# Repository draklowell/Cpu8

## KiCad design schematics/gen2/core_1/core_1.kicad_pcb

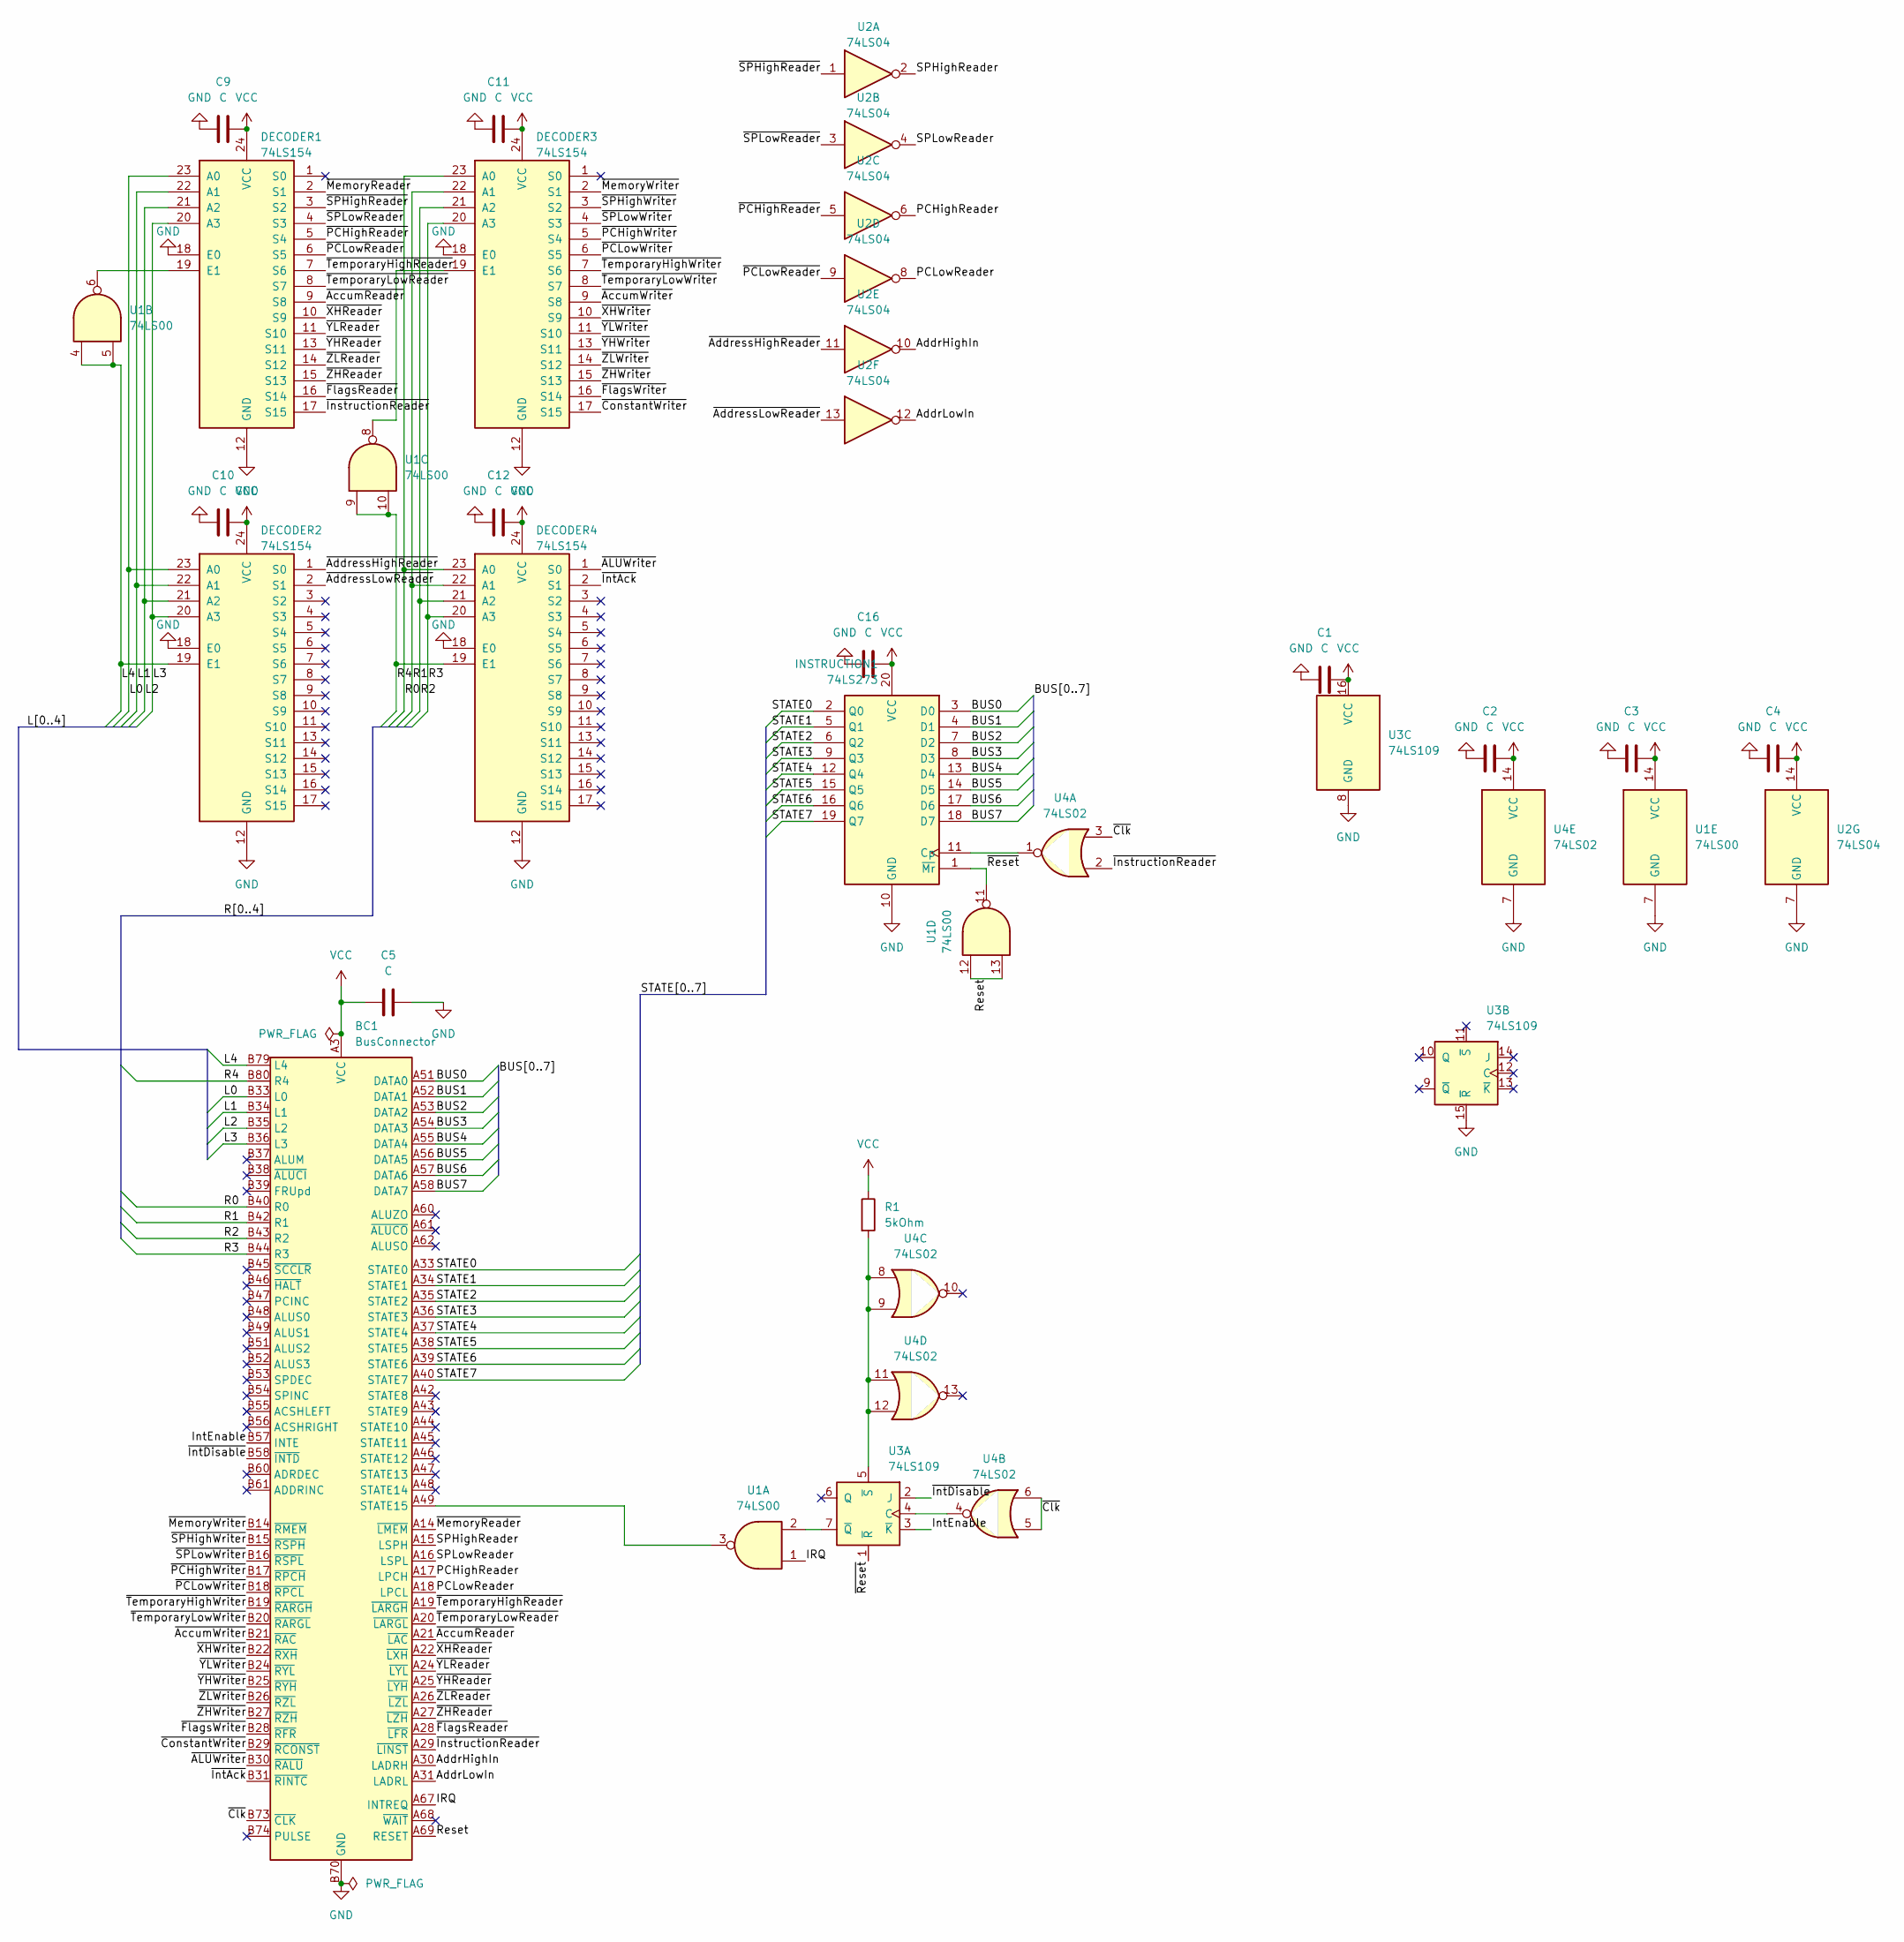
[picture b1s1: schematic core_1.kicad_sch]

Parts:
BC1: BusConnector; BUS_PCIexpress_x16
C1, C2, C3, C4, C9, C10, C11, C12, C16: C; C_Disc_D5.0mm_W2.5mm_P2.50mm
C5: C; C_Radial_D6.3mm_H5.0mm_P2.50mm
DECODER1, DECODER2, DECODER3, DECODER4: 74LS154; DIP-24_W7.62mm_Socket_LongPads
INSTRUCTION1: 74LS273; DIP-20_W7.62mm_Socket_LongPads
R1: 5kOhm; R_Axial_DIN0207_L6.3mm_D2.5mm_P7.62mm_Horizontal
U1: 74LS00; DIP-14_W7.62mm_Socket_LongPads
U2: 74LS04; DIP-14_W7.62mm_Socket_LongPads
U3: 74LS109; DIP-16_W7.62mm_Socket_LongPads
U4: 74LS02; DIP-14_W7.62mm_Socket_LongPads

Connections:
/AddrHighIn: BC1.A30 (LADRH), U2.10
/AddrLowIn: BC1.A31 (LADRL), U2.12
/BUS0: BC1.A51 (DATA0), INSTRUCTION1.3 (D0)
/BUS1: BC1.A52 (DATA1), INSTRUCTION1.4 (D1)
/BUS2: BC1.A53 (DATA2), INSTRUCTION1.7 (D2)
/BUS3: BC1.A54 (DATA3), INSTRUCTION1.8 (D3)
/BUS4: BC1.A55 (DATA4), INSTRUCTION1.13 (D4)
/BUS5: BC1.A56 (DATA5), INSTRUCTION1.14 (D5)
/BUS6: BC1.A57 (DATA6), INSTRUCTION1.17 (D6)
/BUS7: BC1.A58 (DATA7), INSTRUCTION1.18 (D7)
/IRQ: BC1.A67 (INTREQ), U1.1
/IntEnable: BC1.B57 (INTE), U3.3 (~K)
/L0: BC1.B33 (L0), DECODER1.23 (A0), DECODER2.23 (A0)
/L1: BC1.B34 (L1), DECODER1.22 (A1), DECODER2.22 (A1)
/L2: BC1.B35 (L2), DECODER1.21 (A2), DECODER2.21 (A2)
/L3: BC1.B36 (L3), DECODER1.20 (A3), DECODER2.20 (A3)
/L4: BC1.B79 (L4), DECODER2.19 (E1), U1.4, U1.5
/PCHighReader: BC1.A17 (LPCH), U2.6
/PCLowReader: BC1.A18 (LPCL), U2.8
/R0: BC1.B40 (R0), DECODER3.23 (A0), DECODER4.23 (A0)
/R1: BC1.B42 (R1), DECODER3.22 (A1), DECODER4.22 (A1)
/R2: BC1.B43 (R2), DECODER3.21 (A2), DECODER4.21 (A2)
/R3: BC1.B44 (R3), DECODER3.20 (A3), DECODER4.20 (A3)
/R4: BC1.B80 (R4), DECODER4.19 (E1), U1.9, U1.10
/Reset: BC1.A69 (RESET), U1.12, U1.13
/SPHighReader: BC1.A15 (LSPH), U2.2
/SPLowReader: BC1.A16 (LSPL), U2.4
/STATE0: BC1.A33 (STATE0), INSTRUCTION1.2 (Q0)
/STATE1: BC1.A34 (STATE1), INSTRUCTION1.5 (Q1)
/STATE2: BC1.A35 (STATE2), INSTRUCTION1.6 (Q2)
/STATE3: BC1.A36 (STATE3), INSTRUCTION1.9 (Q3)
/STATE4: BC1.A37 (STATE4), INSTRUCTION1.12 (Q4)
/STATE5: BC1.A38 (STATE5), INSTRUCTION1.15 (Q5)
/STATE6: BC1.A39 (STATE6), INSTRUCTION1.16 (Q6)
/STATE7: BC1.A40 (STATE7), INSTRUCTION1.19 (Q7)
/~ALUWriter: BC1.B30 (~RALU), DECODER4.1 (S0)
/~AccumReader: BC1.A21 (~LAC), DECODER1.9 (S8)
/~AccumWriter: BC1.B21 (~RAC), DECODER3.9 (S8)
/~AddressHighReader: DECODER2.1 (S0), U2.11
/~AddressLowReader: DECODER2.2 (S1), U2.13
/~Clk: BC1.B73 (~CLK), U4.3, U4.5, U4.6
/~ConstantWriter: BC1.B29 (~RCONST), DECODER3.17 (S15)
/~FlagsReader: BC1.A28 (~LFR), DECODER1.16 (S14)
/~FlagsWriter: BC1.B28 (~RFR), DECODER3.16 (S14)
/~InstructionReader: BC1.A29 (~LINST), DECODER1.17 (S15), U4.2
/~IntAck: BC1.B31 (~RINTC), DECODER4.2 (S1)
/~IntDisable: BC1.B58 (~INTD), U3.2 (J)
/~MemoryReader: BC1.A14 (~LMEM), DECODER1.2 (S1)
/~MemoryWriter: BC1.B14 (~RMEM), DECODER3.2 (S1)
/~PCHighReader: DECODER1.5 (S4), U2.5
/~PCHighWriter: BC1.B17 (~RPCH), DECODER3.5 (S4)
/~PCLowReader: DECODER1.6 (S5), U2.9
/~PCLowWriter: BC1.B18 (~RPCL), DECODER3.6 (S5)
/~Reset: INSTRUCTION1.1 (~Mr), U1.11, U3.1 (~R)
/~SPHighReader: DECODER1.3 (S2), U2.1
/~SPHighWriter: BC1.B15 (~RSPH), DECODER3.3 (S2)
/~SPLowReader: DECODER1.4 (S3), U2.3
/~SPLowWriter: BC1.B16 (~RSPL), DECODER3.4 (S3)
/~TemporaryHighReader: BC1.A19 (~LARGH), DECODER1.7 (S6)
/~TemporaryHighWriter: BC1.B19 (~RARGH), DECODER3.7 (S6)
/~TemporaryLowReader: BC1.A20 (~LARGL), DECODER1.8 (S7)
/~TemporaryLowWriter: BC1.B20 (~RARGL), DECODER3.8 (S7)
/~XHReader: BC1.A22 (~LXH), DECODER1.10 (S9)
/~XHWriter: BC1.B22 (~RXH), DECODER3.10 (S9)
/~YHReader: BC1.A25 (~LYH), DECODER1.13 (S11)
/~YHWriter: BC1.B25 (~RYH), DECODER3.13 (S11)
/~YLReader: BC1.A24 (~LYL), DECODER1.11 (S10)
/~YLWriter: BC1.B24 (~RYL), DECODER3.11 (S10)
/~ZHReader: BC1.A27 (~LZH), DECODER1.15 (S13)
/~ZHWriter: BC1.B27 (~RZH), DECODER3.15 (S13)
/~ZLReader: BC1.A26 (~LZL), DECODER1.14 (S12)
/~ZLWriter: BC1.B26 (~RZL), DECODER3.14 (S12)
GND: BC1.A12 (GND), BC1.A13 (GND), BC1.A23 (GND), BC1.A32 (GND), BC1.A41 (GND), BC1.A50 (GND), BC1.A59 (GND), BC1.A63 (GND), BC1.A64 (GND), BC1.A65 (GND), BC1.A66 (GND), BC1.A70 (GND), BC1.A71 (GND), BC1.A72 (GND), BC1.A73 (GND), BC1.A74 (GND), BC1.A75 (GND), BC1.A76 (GND), BC1.B12 (GND), BC1.B13 (GND), BC1.B23 (GND), BC1.B32 (GND), BC1.B41 (GND), BC1.B50 (GND), BC1.B59 (GND), BC1.B62 (GND), BC1.B63 (GND), BC1.B64 (GND), BC1.B65 (GND), BC1.B66 (GND), BC1.B67 (GND), BC1.B68 (GND), BC1.B69 (GND), BC1.B70 (GND), BC1.B71 (GND), BC1.B72 (GND), BC1.B75 (GND), BC1.B76 (GND), C1.2, C2.2, C3.2, C4.2, C5.2, C9.2, C10.2, C11.2, C12.2, C16.2, DECODER1.12 (GND), DECODER1.18 (E0), DECODER2.12 (GND), DECODER2.18 (E0), DECODER3.12 (GND), DECODER3.18 (E0), DECODER4.12 (GND), DECODER4.18 (E0), INSTRUCTION1.10 (GND), U1.7 (GND), U2.7 (GND), U3.8 (GND), U3.15 (~R), U4.7 (GND)
unnamed: BC1.A49 (STATE15), U1.3
unnamed: DECODER1.19 (E1), U1.6
unnamed: DECODER3.19 (E1), U1.8
unnamed: INSTRUCTION1.11 (Cp), U4.1
unnamed: U3.4 (C), U4.4
unnamed: U1.2, U3.7 (~Q)
unnamed: R1.2, U3.5 (~S), U4.8, U4.9, U4.11, U4.12
VCC: BC1.A1 (VCC), BC1.A2 (VCC), BC1.A3 (VCC), BC1.A4 (VCC), BC1.A5 (VCC), BC1.B1 (VCC), BC1.B2 (VCC), BC1.B3 (VCC), BC1.B4 (VCC), BC1.B5 (VCC), C1.1, C2.1, C3.1, C4.1, C5.1, C9.1, C10.1, C11.1, C12.1, C16.1, DECODER1.24 (VCC), DECODER2.24 (VCC), DECODER3.24 (VCC), DECODER4.24 (VCC), INSTRUCTION1.20 (VCC), R1.1, U1.14 (VCC), U2.14 (VCC), U3.16 (VCC), U4.14 (VCC)

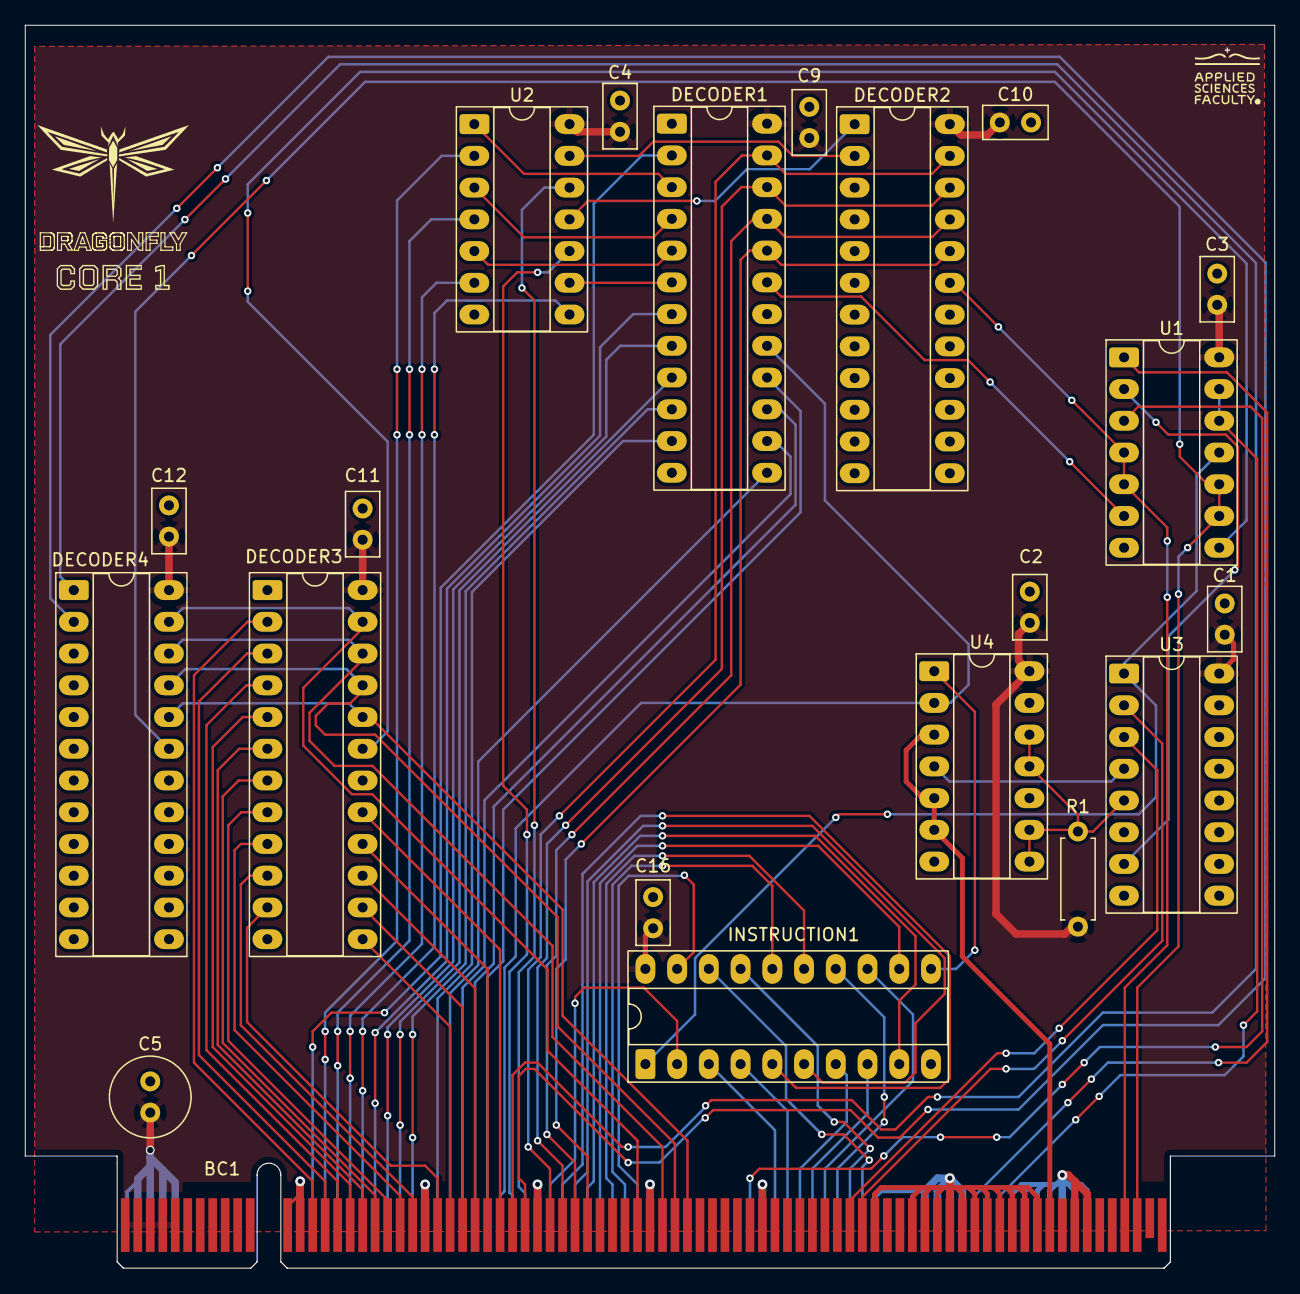
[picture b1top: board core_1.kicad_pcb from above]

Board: 2 copper layers, 100.0 x 99.5 mm, 22 parts (0 on the bottom side), 81 nets.

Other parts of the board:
kibuzzard-6911CC41: G***; kibuzzard-6911CC41

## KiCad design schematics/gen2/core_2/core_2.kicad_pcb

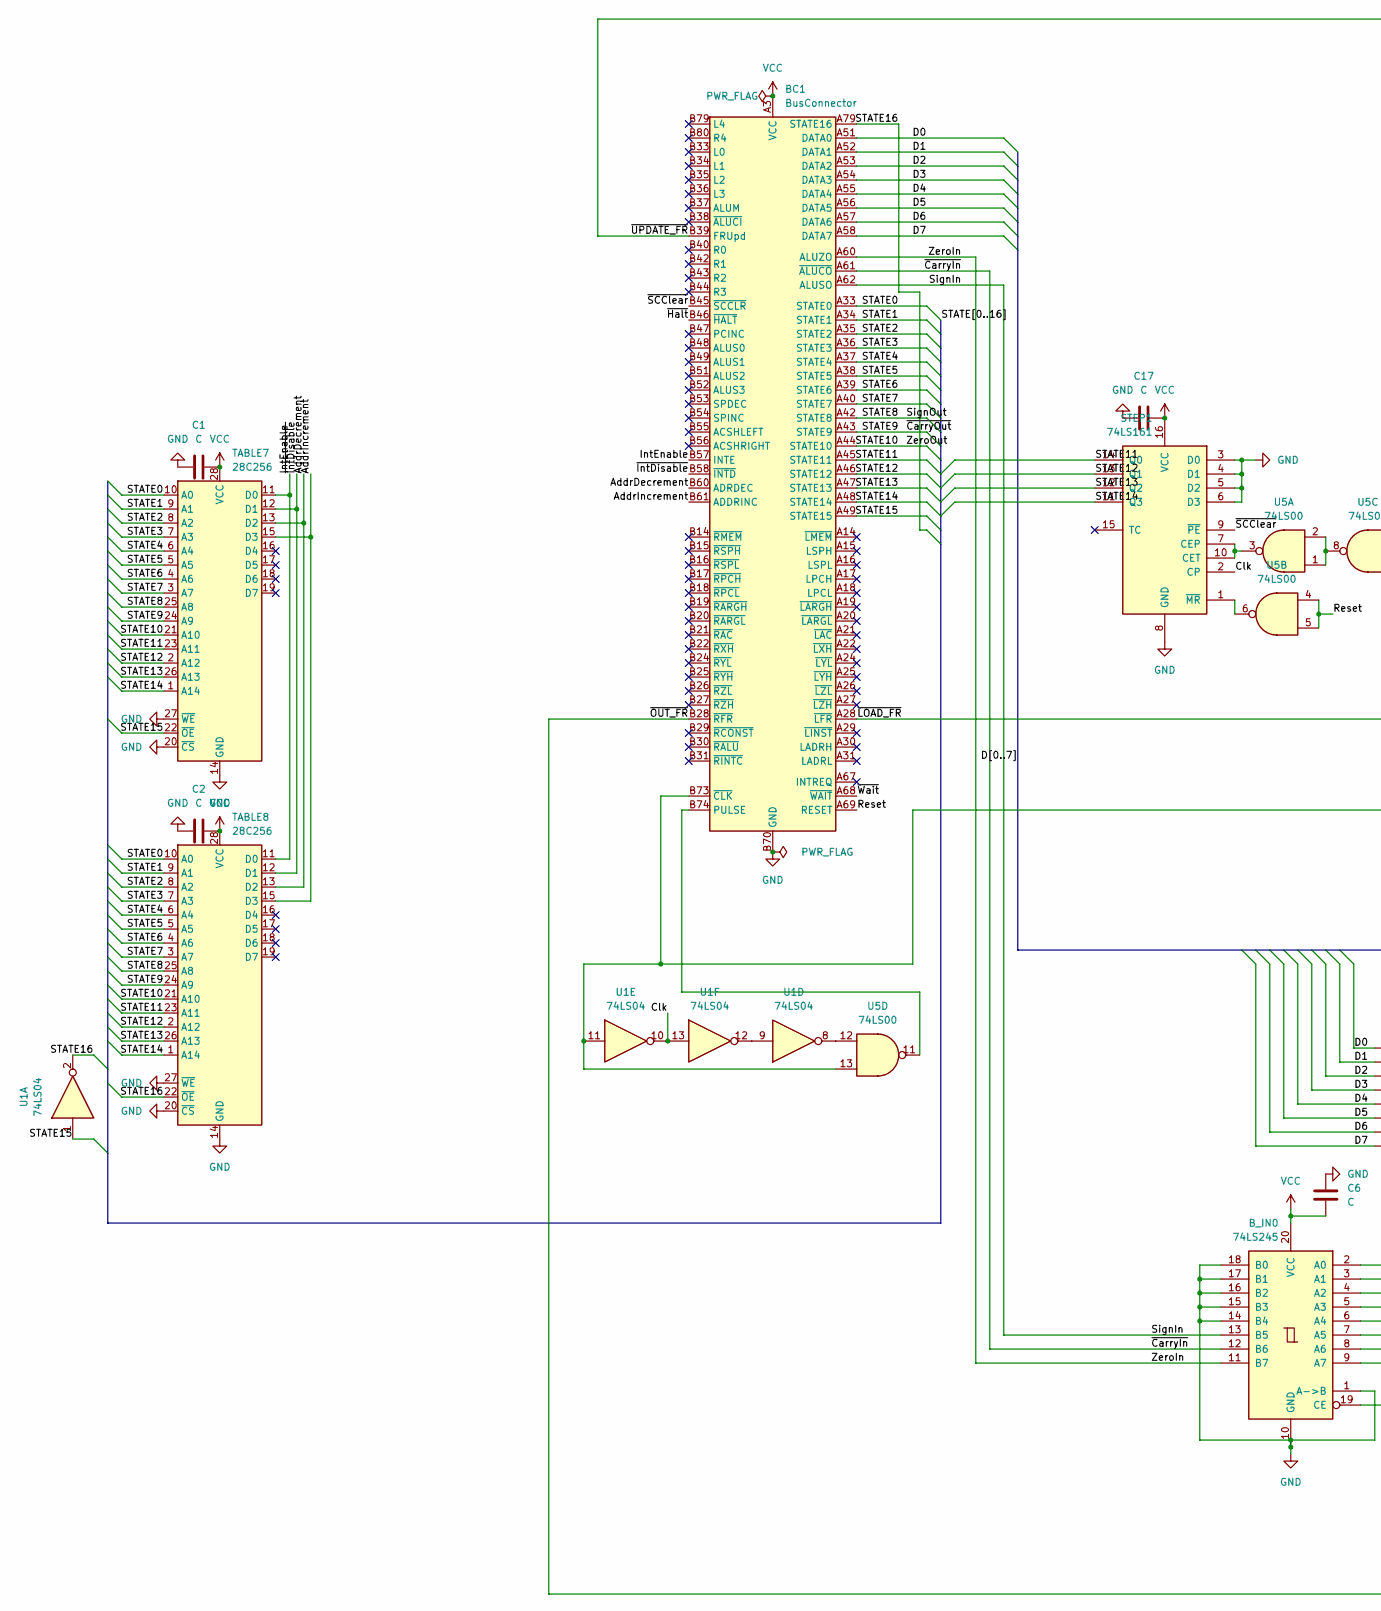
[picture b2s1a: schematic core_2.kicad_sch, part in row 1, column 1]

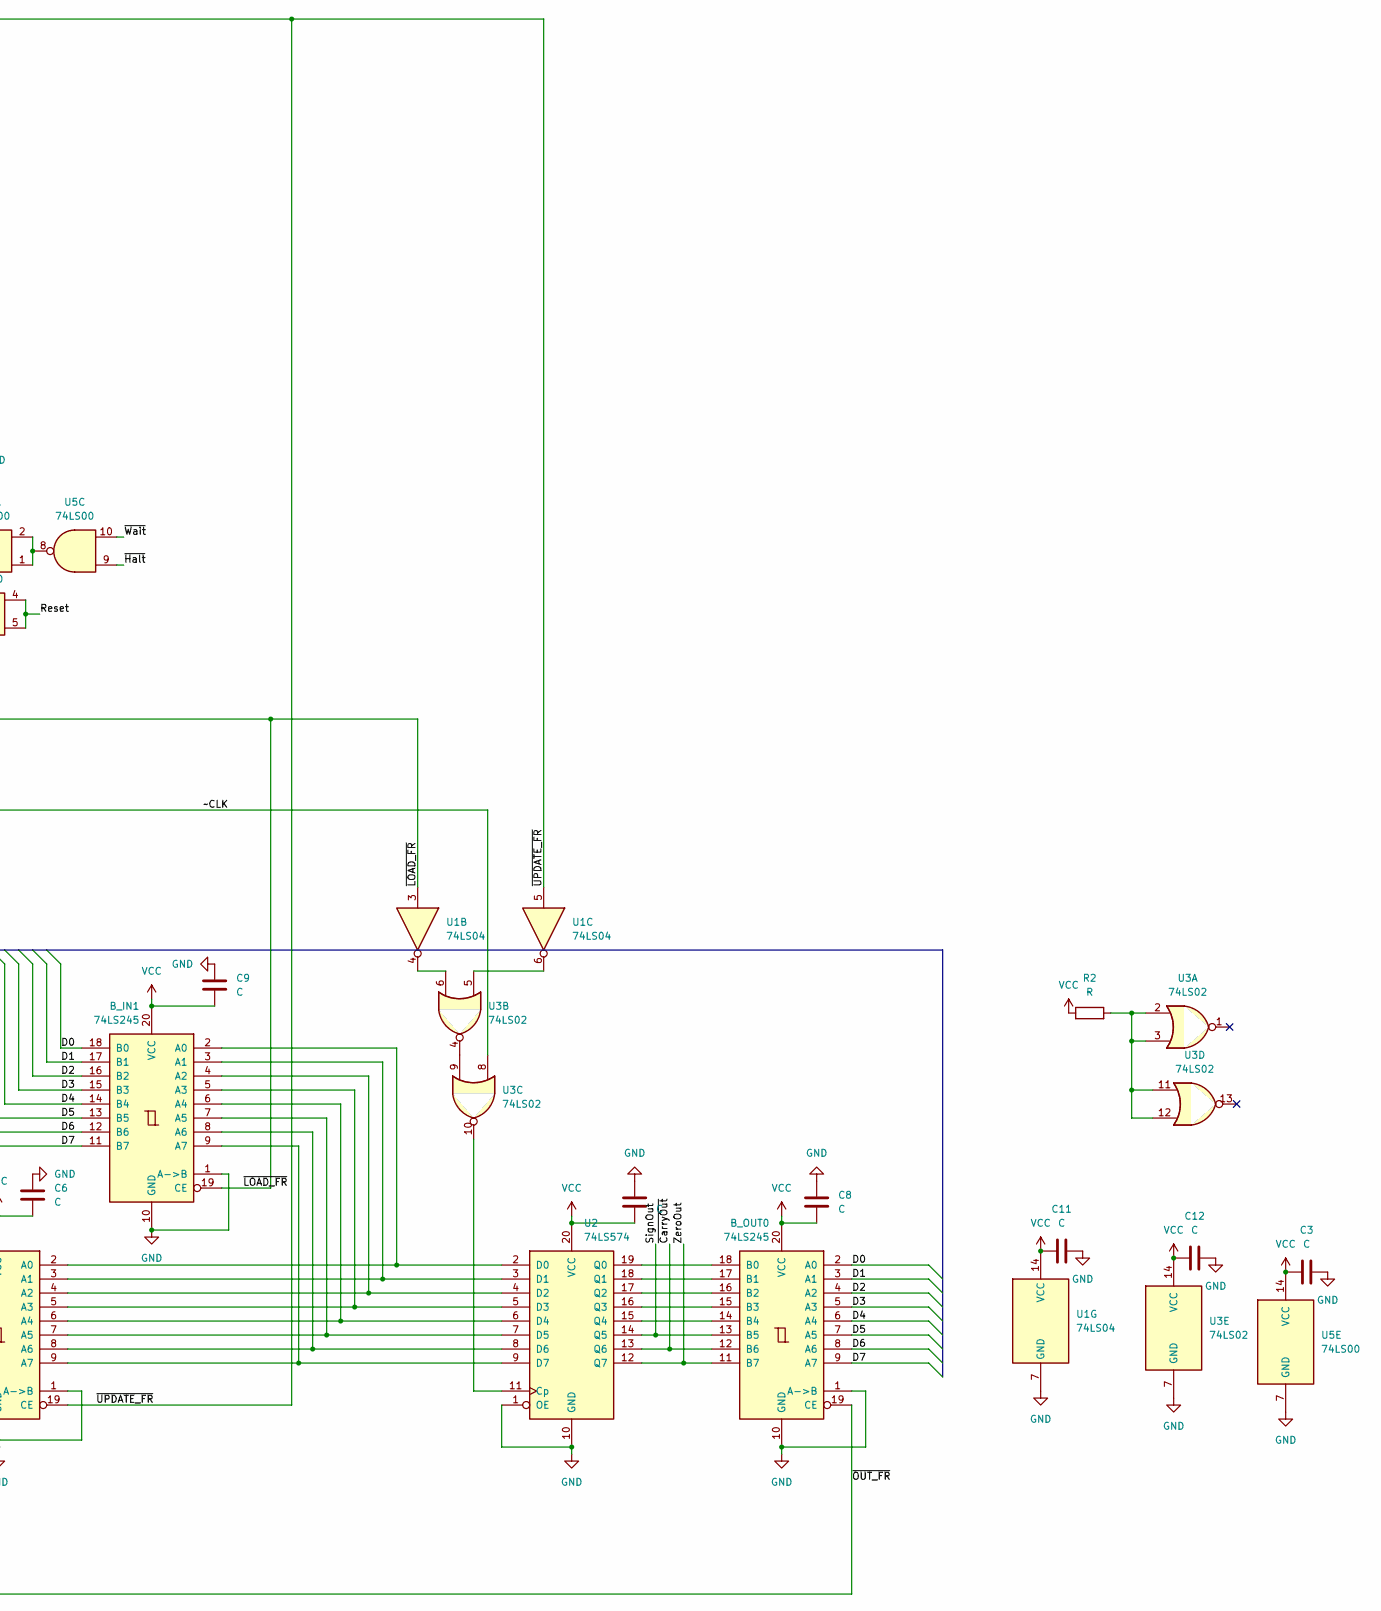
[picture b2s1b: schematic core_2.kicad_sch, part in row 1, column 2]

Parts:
BC1: BusConnector; BUS_PCIexpress_x16
B_IN0, B_IN1: 74LS245; DIP-20_W7.62mm_Socket_LongPads
B_OUT0: 74LS245; DIP-20_W7.62mm_Socket_LongPads
C1, C2, C3, C6, C7, C8, C9, C11, C12, C17: C; C_Disc_D5.0mm_W2.5mm_P5.00mm
R2: R; R_Axial_DIN0207_L6.3mm_D2.5mm_P7.62mm_Horizontal
STEP1: 74LS161; DIP-16_W7.62mm_Socket_LongPads
TABLE7, TABLE8: 28C256; DIP-28_W15.24mm_Socket_LongPads
U1: 74LS04; DIP-14_W7.62mm_Socket_LongPads
U2: 74LS574; DIP-20_W7.62mm_Socket_LongPads
U3: 74LS02; DIP-14_W7.62mm_Socket_LongPads
U5: 74LS00; DIP-14_W7.62mm_Socket_LongPads

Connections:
/AddrDecrement: BC1.B60 (ADRDEC), TABLE7.13 (D2), TABLE8.13 (D2)
/AddrIncrement: BC1.B61 (ADDRINC), TABLE7.15 (D3), TABLE8.15 (D3)
/Clk: STEP1.2 (CP), U1.10, U1.13
/D0: BC1.A51 (DATA0), B_IN1.18 (B0), B_OUT0.2 (A0)
/D1: BC1.A52 (DATA1), B_IN1.17 (B1), B_OUT0.3 (A1)
/D2: BC1.A53 (DATA2), B_IN1.16 (B2), B_OUT0.4 (A2)
/D3: BC1.A54 (DATA3), B_IN1.15 (B3), B_OUT0.5 (A3)
/D4: BC1.A55 (DATA4), B_IN1.14 (B4), B_OUT0.6 (A4)
/D5: BC1.A56 (DATA5), B_IN1.13 (B5), B_OUT0.7 (A5)
/D6: BC1.A57 (DATA6), B_IN1.12 (B6), B_OUT0.8 (A6)
/D7: BC1.A58 (DATA7), B_IN1.11 (B7), B_OUT0.9 (A7)
/IntEnable: BC1.B57 (INTE), TABLE7.11 (D0), TABLE8.11 (D0)
/Reset: BC1.A69 (RESET), U5.4, U5.5
/STATE0: BC1.A33 (STATE0), TABLE7.10 (A0), TABLE8.10 (A0)
/STATE1: BC1.A34 (STATE1), TABLE7.9 (A1), TABLE8.9 (A1)
/STATE2: BC1.A35 (STATE2), TABLE7.8 (A2), TABLE8.8 (A2)
/STATE3: BC1.A36 (STATE3), TABLE7.7 (A3), TABLE8.7 (A3)
/STATE4: BC1.A37 (STATE4), TABLE7.6 (A4), TABLE8.6 (A4)
/STATE5: BC1.A38 (STATE5), TABLE7.5 (A5), TABLE8.5 (A5)
/STATE6: BC1.A39 (STATE6), TABLE7.4 (A6), TABLE8.4 (A6)
/STATE7: BC1.A40 (STATE7), TABLE7.3 (A7), TABLE8.3 (A7)
/STATE8: BC1.A42 (STATE8), B_OUT0.13 (B5), TABLE7.25 (A8), TABLE8.25 (A8), U2.14 (Q5)
/STATE9: BC1.A43 (STATE9), B_OUT0.12 (B6), TABLE7.24 (A9), TABLE8.24 (A9), U2.13 (Q6)
/STATE10: BC1.A44 (STATE10), B_OUT0.11 (B7), TABLE7.21 (A10), TABLE8.21 (A10), U2.12 (Q7)
/STATE11: BC1.A45 (STATE11), STEP1.14 (Q0), TABLE7.23 (A11), TABLE8.23 (A11)
/STATE12: BC1.A46 (STATE12), STEP1.13 (Q1), TABLE7.2 (A12), TABLE8.2 (A12)
/STATE13: BC1.A47 (STATE13), STEP1.12 (Q2), TABLE7.26 (A13), TABLE8.26 (A13)
/STATE14: BC1.A48 (STATE14), STEP1.11 (Q3), TABLE7.1 (A14), TABLE8.1 (A14)
/STATE15: BC1.A49 (STATE15), TABLE7.22 (~OE), U1.1
/STATE16: BC1.A79 (STATE16), TABLE8.22 (~OE), U1.2
/SignIn: BC1.A62 (ALUSO), B_IN0.13 (B5)
/ZeroIn: BC1.A60 (ALUZO), B_IN0.11 (B7)
/~CLK: BC1.B73 (~CLK), U1.11, U3.8, U5.13
/~CarryIn: BC1.A61 (~ALUCO), B_IN0.12 (B6)
/~Halt: BC1.B46 (~HALT), U5.9
/~IntDisable: BC1.B58 (~INTD), TABLE7.12 (D1), TABLE8.12 (D1)
/~LOAD_FR: BC1.A28 (~LFR), B_IN1.19 (CE), U1.3
/~OUT_FR: BC1.B28 (~RFR), B_OUT0.19 (CE)
/~SCClear: BC1.B45 (~SCCLR), STEP1.9 (~PE)
/~UPDATE_FR: BC1.B39 (FRUpd), B_IN0.19 (CE), U1.5
/~Wait: BC1.A68 (~WAIT), U5.10
GND: BC1.A12 (GND), BC1.A13 (GND), BC1.A23 (GND), BC1.A32 (GND), BC1.A41 (GND), BC1.A50 (GND), BC1.A59 (GND), BC1.A63 (GND), BC1.A64 (GND), BC1.A65 (GND), BC1.A66 (GND), BC1.A70 (GND), BC1.A71 (GND), BC1.A72 (GND), BC1.A73 (GND), BC1.A74 (GND), BC1.A75 (GND), BC1.A76 (GND), BC1.B12 (GND), BC1.B13 (GND), BC1.B23 (GND), BC1.B32 (GND), BC1.B41 (GND), BC1.B50 (GND), BC1.B59 (GND), BC1.B62 (GND), BC1.B63 (GND), BC1.B64 (GND), BC1.B65 (GND), BC1.B66 (GND), BC1.B67 (GND), BC1.B68 (GND), BC1.B69 (GND), BC1.B70 (GND), BC1.B71 (GND), BC1.B72 (GND), BC1.B75 (GND), BC1.B76 (GND), B_IN0.1 (A->B), B_IN0.10 (GND), B_IN0.14 (B4), B_IN0.15 (B3), B_IN0.16 (B2), B_IN0.17 (B1), B_IN0.18 (B0), B_IN1.1 (A->B), B_IN1.10 (GND), B_OUT0.1 (A->B), B_OUT0.10 (GND), C1.2, C2.2, C3.2, C6.1, C7.1, C8.1, C9.1, C11.2, C12.2, C17.2, STEP1.3 (D0), STEP1.4 (D1), STEP1.5 (D2), STEP1.6 (D3), STEP1.8 (GND), TABLE7.14 (GND), TABLE7.20 (~CS), TABLE7.27 (~WE), TABLE8.14 (GND), TABLE8.20 (~CS), TABLE8.27 (~WE), U1.7 (GND), U2.1 (OE), U2.10 (GND), U3.7 (GND), U5.7 (GND); also elsewhere on the board
unnamed: BC1.B74 (PULSE), U5.11
unnamed: B_IN0.2 (A0), B_IN1.2 (A0), U2.2 (D0)
unnamed: B_IN0.3 (A1), B_IN1.3 (A1), U2.3 (D1)
unnamed: B_IN0.4 (A2), B_IN1.4 (A2), U2.4 (D2)
unnamed: B_IN0.5 (A3), B_IN1.5 (A3), U2.5 (D3)
unnamed: B_IN0.6 (A4), B_IN1.6 (A4), U2.6 (D4)
unnamed: B_IN0.7 (A5), B_IN1.7 (A5), U2.7 (D5)
unnamed: B_IN0.8 (A6), B_IN1.8 (A6), U2.8 (D6)
unnamed: B_IN0.9 (A7), B_IN1.9 (A7), U2.9 (D7)
unnamed: B_OUT0.18 (B0), U2.19 (Q0)
unnamed: B_OUT0.17 (B1), U2.18 (Q1)
unnamed: B_OUT0.16 (B2), U2.17 (Q2)
unnamed: B_OUT0.15 (B3), U2.16 (Q3)
unnamed: B_OUT0.14 (B4), U2.15 (Q4)
unnamed: R2.2, U3.2, U3.3, U3.11, U3.12
unnamed: STEP1.7 (CEP), STEP1.10 (CET), U5.3
unnamed: STEP1.1 (~MR), U5.6
unnamed: U1.4, U3.6
unnamed: U1.6, U3.5
unnamed: U1.8, U5.12
unnamed: U1.9, U1.12
unnamed: U2.11 (Cp), U3.10
unnamed: U3.4, U3.9
unnamed: U5.1, U5.2, U5.8
VCC: BC1.A1 (VCC), BC1.A2 (VCC), BC1.A3 (VCC), BC1.A4 (VCC), BC1.A5 (VCC), BC1.B1 (VCC), BC1.B2 (VCC), BC1.B3 (VCC), BC1.B4 (VCC), BC1.B5 (VCC), B_IN0.20 (VCC), B_IN1.20 (VCC), B_OUT0.20 (VCC), C1.1, C2.1, C3.1, C6.2, C7.2, C8.2, C9.2, C11.1, C12.1, C17.1, R2.1, STEP1.16 (VCC), TABLE7.28 (VCC), TABLE8.28 (VCC), U1.14 (VCC), U2.20 (VCC), U3.14 (VCC), U5.14 (VCC); also elsewhere on the board

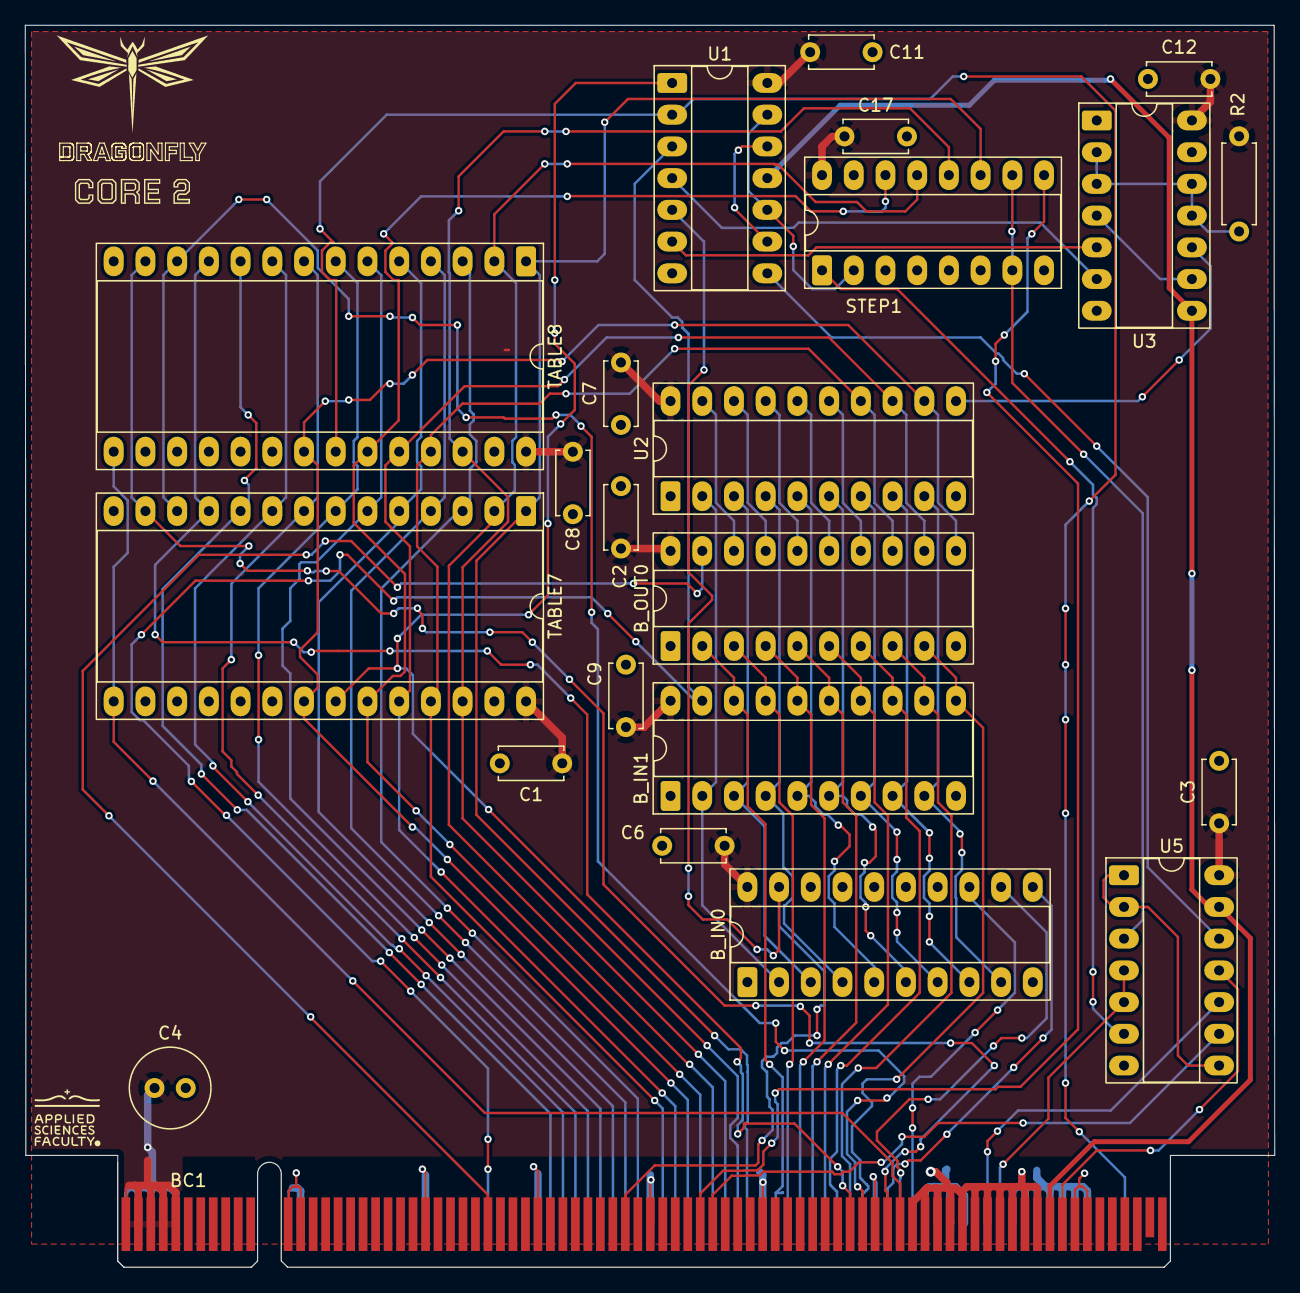
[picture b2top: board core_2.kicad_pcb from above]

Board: 2 copper layers, 100.0 x 99.5 mm, 24 parts (0 on the bottom side), 67 nets.

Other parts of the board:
C4: C; C_Radial_D6.3mm_H5.0mm_P2.50mm
kibuzzard-6911C9E9: G***; kibuzzard-6911C9E9

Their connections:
GND: C4.2; also elsewhere on the board
VCC: C4.1; also elsewhere on the board
